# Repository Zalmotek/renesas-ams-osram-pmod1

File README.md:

# PMOD Sensor Evaluation kit AMS Osram
https://zalmotek.com/products/PMOD-AMS-OSRAM-Sensor-EK/

### Hardware 
#### Overview

The evaluation kit contains the following sensors from AMS-Osram: TMF8828 (a direct time-of-flight (dToF) sensor), AS 7331 (a low-power, low noise integrated UV sensor), AS 7343 (a 14-channel highly versatile, multi-purpose spectral sensor) on a single PMOD enabled board that is compatible with the Renesas QC-IoT System and QC-Studio.

### Hardware components used

#### TMF8828

The TMF8828 is a direct time-of-flight (dToF) sensor in a single modular package with associated VCSEL. The dToF device is based on SPAD, TDC and histogram technology and achieves 5000 mm detection range. Due to its lens on the SPAD, it supports 3x3, 4x4, 3x6 and 8x8 multizone output data and a wide, dynamically adjustable, field of view. A multi-lens-array (MLA) inside the package above the VCSEL widens up the FoI (field of illumination). All processing of the raw data is performed on-chip and the TMF8828 provides distance information together with confidence values on its I2C interface.
Datasheet can be found [here](https://ams-osram.com/products/sensors/distance-proximity-sensors/ams-tmf8828-configurable-8x8-multi-zone-time-of-flight-sensor#Datasheets).

#### AS7343

The AS7343 is a 14-channel highly versatile, multi-purpose spectral sensor enabling new consumer, commercial, industrial and laboratory applications. It is optimized for reflective, transmissive and emissive measurements including color matching, fluid or reagent analysis or general spectral reconstruction.
The spectral response is defined by individual channels covering approximately 380 nm to 1000 nm with 12+2 channels: 12 in the visible spectrum (VIS) to near-infrared (NIR) range, a clear channel and flicker channel. Applications can be assisted by full spectral reconstruction of light and an integrated flicker detection channel that can automatically flag ambient light flicker at 50/60 Hz as well as buffer data for externally calculating other flicker frequencies.

AS7343 integrates high-precision optical filters onto standard CMOS silicon via deposited interference filter technology. A built-in aperture controls the light entering the sensor array to increase accuracy. A programmable digital GPIO and LED driver enable light source and trigger/sync control. Device control and spectral data access is implemented through a serial I²C interface. The device is available in an ultra-low profile package with dimensions of 3.1 mm x 2 mm x 1 mm.

Datasheet can be found [here](https://ams-osram.com/products/sensors/ambient-light-color-spectral-sensors/ams-as7343-spectral-sensor#Datasheets).

#### AS7331

The AS7331 is a low-power, low noise integrated UV sensor. The three separated UVA, UVB and UVC channels convert optical radiation signals via UV optimized photodiodes to a digital result and realize a continuous or triggered measurement. The irradiance responsivity can be adjusted via Gain, conversion time and internal clock frequency to effect sensitivity, full scale range and LSB. The AS7331 offers a range of 12 Gain steps by a factor of two for each step. The conversion time is internally controlled over a wide range of 15 steps by a factor of two for each step. With the input pin (SYN), the conversion time can be externally controlled to adapt the measurement to the given environment and time base.

With its irradiance responsiveness factor and conversion time, the AS7331 supports an overall huge dynamic range up to 3.43E+10 (resolution multiplied by gain range). It achieves an accuracy of up to 24-bit signal resolution (internal via I²C and shifter 16-bit), with an irradiance responsivity per count down to 2.38 nW/cm² at 64 ms integration time. Via an integrated divider, the 16-bit I²C output can be adjusted to the significant bits of interest.

Datasheet can be found [here](https://ams-osram.com/products/sensors/ambient-light-color-spectral-sensors/ams-as7331-spectral-uv-sensor#Datasheets).

### Firmware 

**FSP version: 4.5.0**

The repository contains the following firmware samples: 

[*EKRA2E1_AS7331_SCI_IIC*](firmware\AS7331\EKRA2E1_AS7331_SCI_IIC.zip)

This sample was configured for the EK-RA2E1 Evaluation Kit and it reads and outputs data from the AS7331 UV A/B/C light sensor. The following output example shows how the firmware reads the raw UV values collected by the sensor and scales them. Additionally, the firmware reads the temperature values from the on-board temperature sensor and outputs them via SEGGER’s RTT.

Video demo: https://www.youtube.com/watch?v=bvvvC9w7Clc

[*EKRA2E1_AS7343_SCI_IIC*](firmware\AS7343\EKRA2E1_AS7343_SCI_IIC.zip)

This sample was configured for the EK-RA2E1 Evaluation Kit. It uses the AS7343 14-channel spectral sensor to measure the intensity of particular wavelengths of light and outputs them via RTT.

Video Demo: https://www.youtube.com/watch?v=52XaccK38CQ

[*EKRA2E1_TMF8828_SCI_IIC*](firmware/TMF8828/EKRA2E1_TMF8828_SCI_IIC.zip)

This sample was configured for the EK-RA2E1 Evaluation Kit and it reads and outputs data from the TMF8828 8x8 multi-zone ToF sensor. This firmware measures distances to the subject for each point of the measurement matrix and outputs them via RTT.

Video Demo: https://www.youtube.com/watch?v=_Tr8oC4eRQ4 

[*EKRA6M4_AS7331_IIC*](firmware\AS7331\EKRA6M4_AS7331_IIC.zip)

This sample was configured for the EK-RA6M4 Evaluation Kit and it reads and outputs data from the AS7331 UV A/B/C light sensor. The following output example shows how the firmware reads the raw UV values collected by the sensor and scales them. Additionally, the firmware reads the temperature values from the on-board temperature sensor and outputs them via SEGGER’s RTT.

Video demo: https://www.youtube.com/watch?v=bvvvC9w7Clc

[*EKRA6M4_AS7343_IIC*](firmware\AS7343\EKRA6M4_AS7343_IIC.zip)

This sample was configured for the EK-RA6M4 Evaluation Kit. It uses the AS7343 14-channel spectral sensor to measure the intensity of particular wavelengths of light and outputs them via RTT.

Video Demo: https://www.youtube.com/watch?v=52XaccK38CQ

[*EKRA6M4_TMF8828_IIC*](firmware\TMF8828\EKRA6M4_TMF8828_IIC.zip)

This sample was configured for the EK-RA6M4 Evaluation Kit and it reads and outputs data from the TMF8828 8x8 multi-zone ToF sensor. This firmware measures distances to the subject for each point of the measurement matrix and outputs them via RTT.

Video Demo: https://www.youtube.com/watch?v=_Tr8oC4eRQ4 

#  Quick-Start Guide

## Configuring Pmod1 to support Pmod Type 6A (I2C)

Before we begin setting up anything on the software side of things we need to enable I2C support on the Pmod interface. On both the EK-RA2E1 and the EK-RA6M4 Evaluation Kits only the Pmod1 interface can be configured to support I2C connections.

According to the EK-RA2E1 [user’s manual](https://www.renesas.com/us/en/document/man/ek-ra2e1-v1-users-manual), more specifically Table 13 found on page 19, we need to short the E18 and E19 jumpers and open the  E14 and E15 jumpers found on the back of the board.

Following the EK-RA6M4 [user’s manual](https://www.renesas.com/us/en/document/mat/ek-ra6m4-v1-users-manual), table 13 found on page 17, we need to short the E36 and E37 jumpers  and open the E29 and E33 jumpers found on the back of the board.

## Setting up e2 studio IDE

Download and install the latest version of [e2 studio IDE](https://www.renesas.com/us/en/software-tool/e-studio), making sure to install FSP4.6.0 and FSP4.5.0, support for the RA an RZ family and the GNU Arm Embedded 12.2.1 toolchain.

### EK-RA2E1

#### Creating the project
To create a new project go to **File -> New -> Renesas C/C++ Project -> Renesas RA**. Select the** Renesas RA C/C++ Project** template. After giving the project a fitting name you’ll be prompted to select the FSP Version, Board, Language, Toolchain and the Debugger. For the FSP Version select the latest one available (at the time of writing it’s **4.5.0**), the board needs to be EK-RA2E1, for the language check **C++**, the toolchain should be the latest available (at the time of writing it’s **GNU Arm Embedded 12.2.1** ) and for the Debugger select J-Link ARM. For this sample you can leave the default values of **Executable and No RTOS**. On the next screen select **Bare Metal - Minimal** and click **Finish**.

#### Configuring the stacks 

For this board we need to include the r_sci_i2c stack as it is the only one that works with I2C channel 2, the channel that gets routed to the Pmod interface. We now need to head out to the properties tab and select the appropriate channel 2 and the corresponding slave address. Make sure to select Fast-mode rate and fill in the Callback with i2c_master_callback.

One of the samples also needs the r_agt Low-Power Timer stack in order for it to work. We also need to configure it by changing the Mode to Periodic, channel to 0, Period Unit to 0xFFFF and Count Source to LOCO.

### EK-RA6M4

#### Creating the project

To create a new project go to File -> New -> Renesas C/C++ Project -> Renesas RA. Select the Renesas RA C/C++ Project template. After giving the project a fitting name you’ll be prompted to select the FSP Version, Board, Language, Toolchain and the Debugger. For the FSP Version select the latest one available (at the time of writing it’s 4.6), the board needs to be EK-RA6M4, for the language check C++, the toolchain should be the latest available (at the time of writing it’s GNU Arm Embedded 12.2.1) and for the Debugger select J-Link ARM. For this sample you can leave the default values of Executable and No RTOS. On the next screen select Bare Metal - Minimal and click Finish.

#### Configuring the stacks

For this board we need to include the r_iic_master stack as it is the only one that works with I2C channel 1, the channel that gets routed to the Pmod interface. We now need to head out to the properties tab and select the appropriate channel 1 and the corresponding slave address. Make sure to select Fast-mode rate and fill in the Callback with i2c_master_callback.

One of the samples also needs the r_agt Low-Power Timer stack in order for it to work. We also need to configure it by changing the Mode to Periodic, channel to 0, Period Unit to 0xFFFF and Count Source to LOCO.

## Header files description

### The i2c_op.h header file

In this header file we have defined some basic functions needed for I2C operations as follows:

The *delay* function takes one integer as an argument and delays the system for the given number of milliseconds.

The *i2c_master_callback* function is the same function we’ve referenced when configuring the I2C stacks. This function updates the i2c_event variable after every I2C operation concludes.

The *validate_i2c_event* function needs to be called after every I2C operation to make sure that there were no errors, mainly timeout or event aborted.

The *I2CStart* function tries to open the I2C bus.

The *I2CRead* function takes 3 arguments as inputs. The buff pointer represents an array which is going to be populated with buff_len number of bytes after the read operation concludes. If the restart argument is set to true then it will send a repeated start condition after the read operation.

The *I2CWrite* function takes 3 arguments as inputs. The buff pointer represents an array from which we will send exactly the first buff_len number of bytes.  If the restart argument is set to true then it will send a repeated start condition after the read operation.

### The Wire library

In this library we have declared 2 arrays: the rx and tx buffers which are going to be used for receiving and transmitting data. Let’s take an in depth look at the functions found here:

The *wire_clear_buffer_n* function takes 2 arguments. The buff pointer represents the buffer that we want to clear and len represents how many bytes we want to erase from it.

The *wire_init_communication* function takes 1 argument, the address of the device we want to communicate with. Inside we initialise the I2C bus and clear both buffers.

The *beginTransmission* function just calls the wire_init_communication function and checks if it was successful.

The *wire_write* function takes the arguments and passes them directly to the I2CWrite function and then clears the tx buffer.

The *wire_read* function first clears the rx buffer then passes the arguments straight to the I2CRead function.

The *wire_read_register* function pushes the register address argument to the tx buffer, sends the buffer and then clears it. If these operations were successful we can read the register value that was sent by the connected device.  

The *requestFrom* function reads the count number of bytes from the connected device.

The *write* function pushes one byte of data to the end of the tx buffer as long as there is space left.

The *read* function returns the one byte of data from the start index of the rx buffer and then moves the index by 1 position.

The *available* function checks if the start index of the rx buffer is the same as the length of the buffer, in which case there is no more data left to process in the buffer.

The *endTransmission* function sends the tx buffer and then clears it.

### The SEGGER_RTT folder

This folder is provided by Renesas and can be found in the Example Project Bundle. Inside it there are files that set up the connection to SEGGER’s RTT so that users can inspect the output of the firmware samples using J-Link RTT Viewer.

## Building and flashing the firmware

In order to build the firmware we need to make sure that we have the correct project selected. We can do this by checking if the *Debug* flag is showing after the project name.

After that we can click the hammer icon located in the top right to build the firmware.

To flash the firmware we need to click the debug icon and pass the debug points by hitting the resume button.

## Debugging
When inspecting the output of the firmware samples, we will use SEGGER’s RTT Viewer. In case it was not included in the default installation of e2 studio, it can be downloaded from [here](https://www.segger.com/products/debug-probes/j-link/tools/rtt-viewer/).

#### EK-RA2E1

In the case of EK-RA2E1, use the following settings for the RTT viewer:

#### EK-RA6M4

In the case of EK-RA6M4, use the following settings for the RTT viewer:

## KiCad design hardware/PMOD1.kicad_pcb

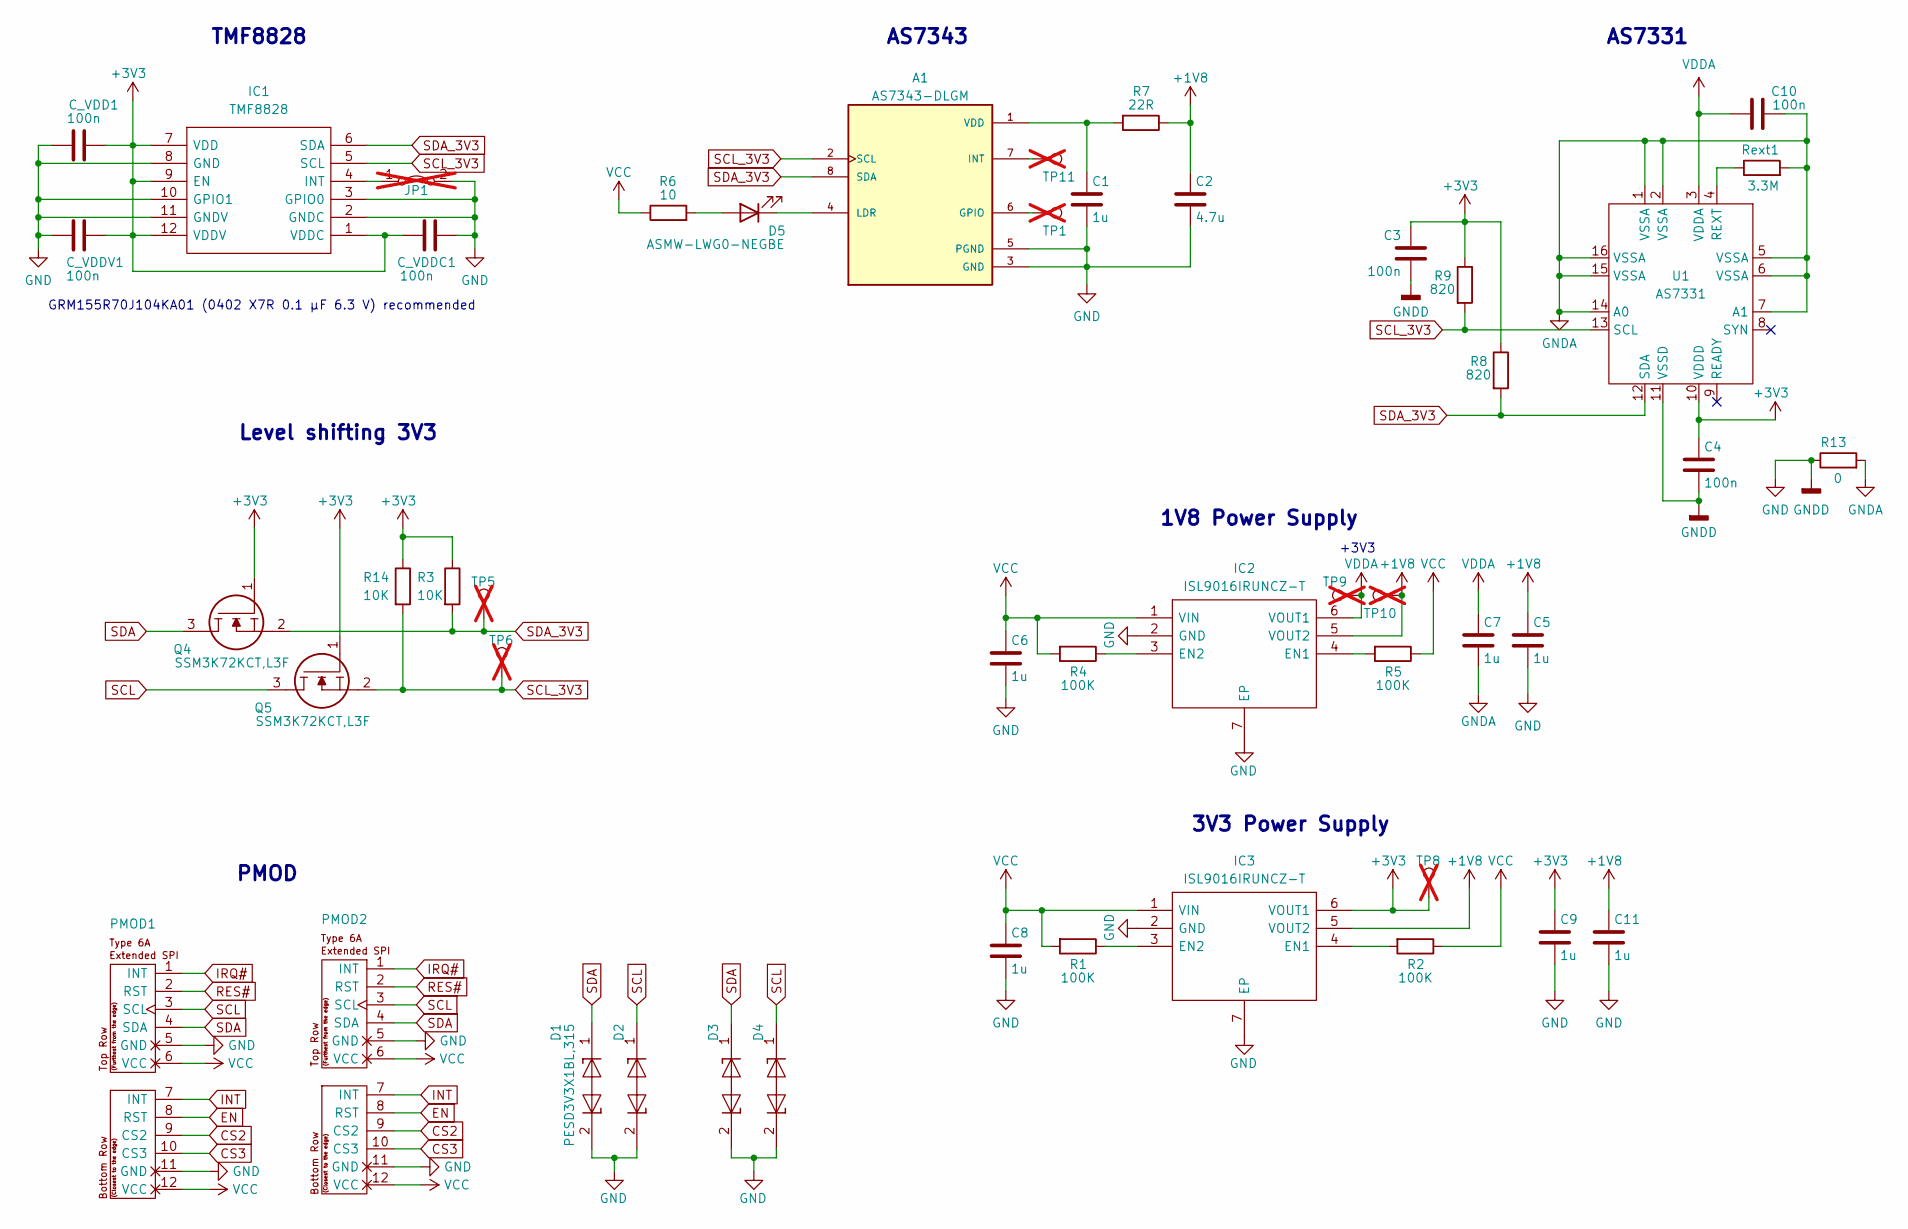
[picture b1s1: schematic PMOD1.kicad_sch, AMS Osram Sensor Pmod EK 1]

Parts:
A1: AS7343-DLGM; XDCR_AS7343-DLGM; PARTREV v2-00
C1, C5, C6, C7, C8, C9, C11: 1u; C_0402_1005Metric
C2: 4.7u; C_0402_1005Metric
C3, C4, C10: 100n; C_0402_1005Metric
C_VDD1: 100n; C_0402_1005Metric
C_VDDC1: 100n; C_0402_1005Metric
C_VDDV1: 100n; C_0402_1005Metric
D1, D2, D3, D4: PESD3V3X1BL,315; PESD5V0S1BL315; Mouser Part Number 771-PESD3V3X1BL,315
D5: ASMW-LWG0-NEGBE; LED_PLCC_2835
IC1: TMF8828; TMF88201AM; Manufacturer_Part_Number TMF8820-1AM
IC2, IC3: ISL9016IRUNCZ-T; SON50P160X160X55-7N; Mouser Part Number 968-ISL9016IRUNCZ-T
JP1: INT_TMF8820; SolderJumper-2_P1.3mm_Bridged2Bar_RoundedPad1.0x1.5mm; not fitted
PMOD1: PMOD-Device-x2-Type-6A-Extended-I2C; PMOD_6A_Male
PMOD2: PMOD-Device-x2-Type-6A-Extended-I2C; PMOD_6A_Female
Q4, Q5: SSM3K72KCT,L3F; SSM3K72KCTL3F; Mouser Part Number 757-SSM3K72KCTL3F
R1, R2, R4, R5: 100K; R_0402_1005Metric
R3, R14: 10K; R_0402_1005Metric
R6: 10; R_0402_1005Metric
R7: 22R; R_0402_1005Metric
R8, R9: 820; R_0402_1005Metric
R13: 0; R_0402_1005Metric
Rext1: 3.3M; R_0402_1005Metric
TP1, TP5, TP6, TP8, TP9, TP10, TP11: GPIO; TestPoint_Pad_D1.0mm; not fitted
U1: AS7331

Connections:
+1V8: C2.1, C5.1, C11.1, IC2.5 (VOUT2), IC3.5 (VOUT2), R7.1, TP10.1
+3V3: C3.2, C4.1, C9.1, C_VDD1.2, C_VDDC1.1, C_VDDV1.1, IC1.1 (VDDC), IC1.7 (VDD), IC1.9 (EN), IC1.12 (VDDV), IC3.6 (VOUT1), Q4.1, Q5.1, R3.1, R8.1, R9.1, R14.1, TP8.1, U1.10 (VDDD)
CS2: PMOD1.9 (CS2), PMOD2.9 (CS2)
CS3: PMOD1.10 (CS3), PMOD2.10 (CS3)
EN: PMOD1.8 (RST), PMOD2.8 (RST)
GND: A1.3 (GND), A1.5 (PGND), C1.2, C2.2, C3.1, C4.2, C5.2, C6.2, C8.2, C9.2, C11.2, C_VDD1.1, C_VDDC1.2, C_VDDV1.2, D1.2, D2.2, D3.2, D4.2, IC1.2 (GNDC), IC1.3 (GPIO0), IC1.8 (GND), IC1.10 (GPIO1), IC1.11 (GNDV), IC2.2 (GND), IC2.7 (EP), IC3.2 (GND), IC3.7 (EP), JP1.2 (B), PMOD1.5 (GND), PMOD1.11 (GND), PMOD2.5 (GND), PMOD2.11 (GND), R13.1, U1.11 (VSSD)
GNDA: C7.2, C10.2, R13.2, Rext1.2, U1.1 (VSSA), U1.2 (VSSA), U1.5 (VSSA), U1.6 (VSSA), U1.7 (A1), U1.14 (A0), U1.15 (VSSA), U1.16 (VSSA)
INT: PMOD1.7 (INT), PMOD2.7 (INT)
IRQ#: PMOD1.1 (INT), PMOD2.1 (INT)
unnamed: A1.6 (GPIO), TP1.1
unnamed: A1.7 (INT), TP11.1
unnamed: A1.4 (LDR), D5.2 (K)
unnamed: A1.1 (VDD), C1.1, R7.2
unnamed: D5.1 (A), R6.2
unnamed: IC1.4 (INT), JP1.1 (A)
unnamed: IC2.4 (EN1), R5.2
unnamed: IC2.3 (EN2), R4.1
unnamed: IC3.4 (EN1), R2.2
unnamed: IC3.3 (EN2), R1.1
unnamed: Rext1.1, U1.4 (REXT)
RES#: PMOD1.2 (RST), PMOD2.2 (RST)
SCL: D2.1, D4.1, PMOD1.3 (SCL), PMOD2.3 (SCL), Q5.3
SCL_3V3: A1.2 (SCL), IC1.5 (SCL), Q5.2, R9.2, R14.2, TP6.1, U1.13 (SCL)
SDA: D1.1, D3.1, PMOD1.4 (SDA), PMOD2.4 (SDA), Q4.3
SDA_3V3: A1.8 (SDA), IC1.6 (SDA), Q4.2, R3.2, R8.2, TP5.1, U1.12 (SDA)
VCC: C6.1, C8.1, IC2.1 (VIN), IC3.1 (VIN), PMOD1.6 (VCC), PMOD1.12 (VCC), PMOD2.6 (VCC), PMOD2.12 (VCC), R1.2, R2.1, R4.2, R5.1, R6.1
VDDA: C7.1, C10.1, IC2.6 (VOUT1), TP9.1, U1.3 (VDDA)

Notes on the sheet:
3V3 Power Supply
AS7331
AS7343
1V8 Power Supply
PMOD
TMF8828
+3V3
Level shifting 3V3
GRM155R70J104KA01 (0402 X7R 0.1 µF 6.3 V) recommended

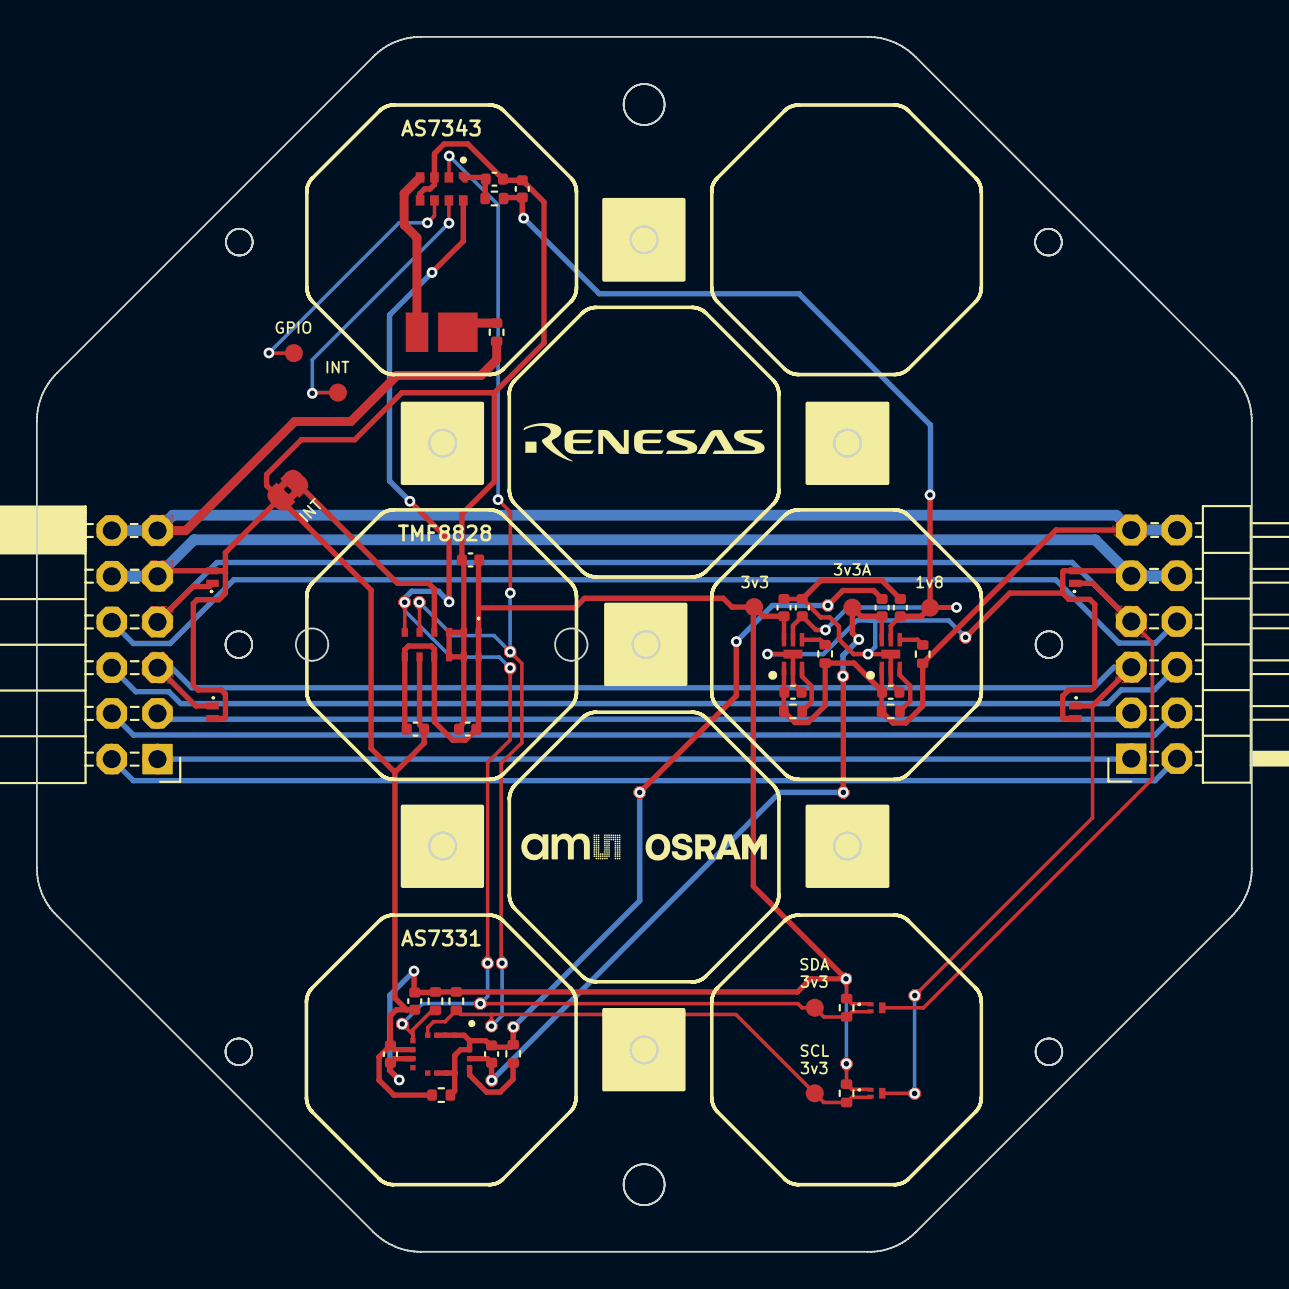
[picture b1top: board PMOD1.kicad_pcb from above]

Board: 2 copper layers, 67.5 x 67.5 mm, 48 parts (0 on the bottom side), 27 nets.

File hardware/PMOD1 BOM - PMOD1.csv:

,,,,,,,,
Item,Reference(s),Value,Manufacturer Name,Footprint,Qty,Link,Pieces Left,Pieces necesarry for 105 (93 already assambled)
1,A1,AS7343-DLGM,AS7343-DLGM,XDCR_AS7343-DLGM,1,https://ro.mouser.com/ProductDetail/ams-OSRAM/AS7343-DLGM?qs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,0,12
2,"C1, C5, C6, C7, C8, C9, C11",1u,04026D105KAT4A,Capacitor_SMD:C_0402_1005Metric,7,https://eu.mouser.com/ProductDetail/KYOCERA-AVX/04026D105KAT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,52,32
3,C2,4.7u,04026D475MAT2A,Capacitor_SMD:C_0402_1005Metric,1,https://eu.mouser.com/ProductDetail/KYOCERA-AVX/04026D475MAT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,92,0
4,"C3, C4, C10, C_VDD1, C_VDDC1, C_VDDV1",100n,04026D104KAT2A,Capacitor_SMD:C_0402_1005Metric,6,https://eu.mouser.com/ProductDetail/KYOCERA-AVX/04026D104KAT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,48,24
5,"D1, D2, D3, D4",,"PESD3V3X1BL,315",DFN-1006-2,4,https://ro.mouser.com/ProductDetail/Nexperia/PESD3V3X1BL315?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,6,42
6,D5,,ASMW-LWG0-NEGBE,LED_SMD:LED_PLCC_2835,1,https://eu.mouser.com/ProductDetail/Broadcom-Avago/ASMW-LWG0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,2,10
7,IC1,TMF8828,TMF8828,TMF8828,1,https://ro.mouser.com/ProductDetail/ams-OSRAM/TMF8828-1AM?qs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,0,20
8,"IC2, IC3","3V3, 1V8",ISL9016IRUNCZ-T,,2,https://eu.mouser.com/ProductDetail/Renesas-Intersil/ISL9016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,6,18
9,PMOD1,,10129382-912002BLF,PMOD:PMOD_6A_Male,1,https://ro.mouser.com/ProductDetail/Amphenol-FCI/10129382-91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,0,12
10,PMOD2,,613012243121,PMOD:PMOD_6A_Female,1,https://ro.mouser.com/ProductDetail/Wurth-Elektronik/6130122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,0,12
11,"Q4, Q5",SSM3K72KCTL3F,"SSM3K72KCT,L3F",SSM3K72KCTL3F,2,https://www.mouser.co.uk/ProductDetail/Toshiba/SSM3K72KCTL3F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,3,21
12,"R3, R14",10K,RK73B1ETTPS103J,Resistor_SMD:R_0402_1005Metric,2,https://eu.mouser.com/ProductDetail/KOA-Speer/RK73B1ETTPS103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,79,0
13,"R1, R2, R4, R5",100k,ERJ-2RKF1003X,Resistor_SMD:R_0402_1005Metric,4,https://ro.mouser.com/ProductDetail/Panasonic/ERJ-2RKF1003X?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,7,41
14,R6,10,CR0402-FX-10R0GLF,Resistor_SMD:R_0402_1005Metric,1,https://ro.mouser.com/ProductDetail/Bourns/CR0402-FX-10R0GLF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,14,0
15,R7,22R,RK73H1ETTP22R0F,Resistor_SMD:R_0402_1005Metric,1,https://eu.mouser.com/ProductDetail/KOA-Speer/RK73H1ETTP22R0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,8,4
16,"R8, R9",820,RK73H1ETTP8200F,Resistor_SMD:R_0402_1005Metric,2,https://eu.mouser.com/ProductDetail/KOA-Speer/RK73H1ETTP8200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,86,0
17,R13,0,CRCW04020000Z0EDC,Resistor_SMD:R_0402_1005Metric,1,https://ro.mouser.com/ProductDetail/Vishay-Dale/CRCW04020000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,94,0
18,Rext1,3.3M,RK73H1ETTP3304F,Resistor_SMD:R_0402_1005Metric,1,https://eu.mouser.com/ProductDetail/KOA-Speer/RK73H1ETTP3304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,91,0
19,U1,AS7331,AS7331-AQFM,AS7331:AS7331,1,https://ro.mouser.com/ProductDetail/ams-OSRAM/AS7331-AQFM?qs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,2,10

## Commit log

2023-10-04 added photos
2023-10-04 added firmware samples
2023-10-04 updated documentation
2023-10-04 modified readme
2023-11-16 added documentation for TMF8828
2023-11-21 Modified the output of some samples for better readability
2023-11-22 Restructured the repository.
2023-11-22 modified screenshots.
2023-11-28 PCB design files
2023-12-04 Updated firmware&documentation.
2023-12-04 renamed folders. Updated documentation.
2023-12-07 updated firmware. updated documentation
2024-02-12 Added C samples. Modified Readme
2024-09-18 cleanup
2024-09-18 reogranized
